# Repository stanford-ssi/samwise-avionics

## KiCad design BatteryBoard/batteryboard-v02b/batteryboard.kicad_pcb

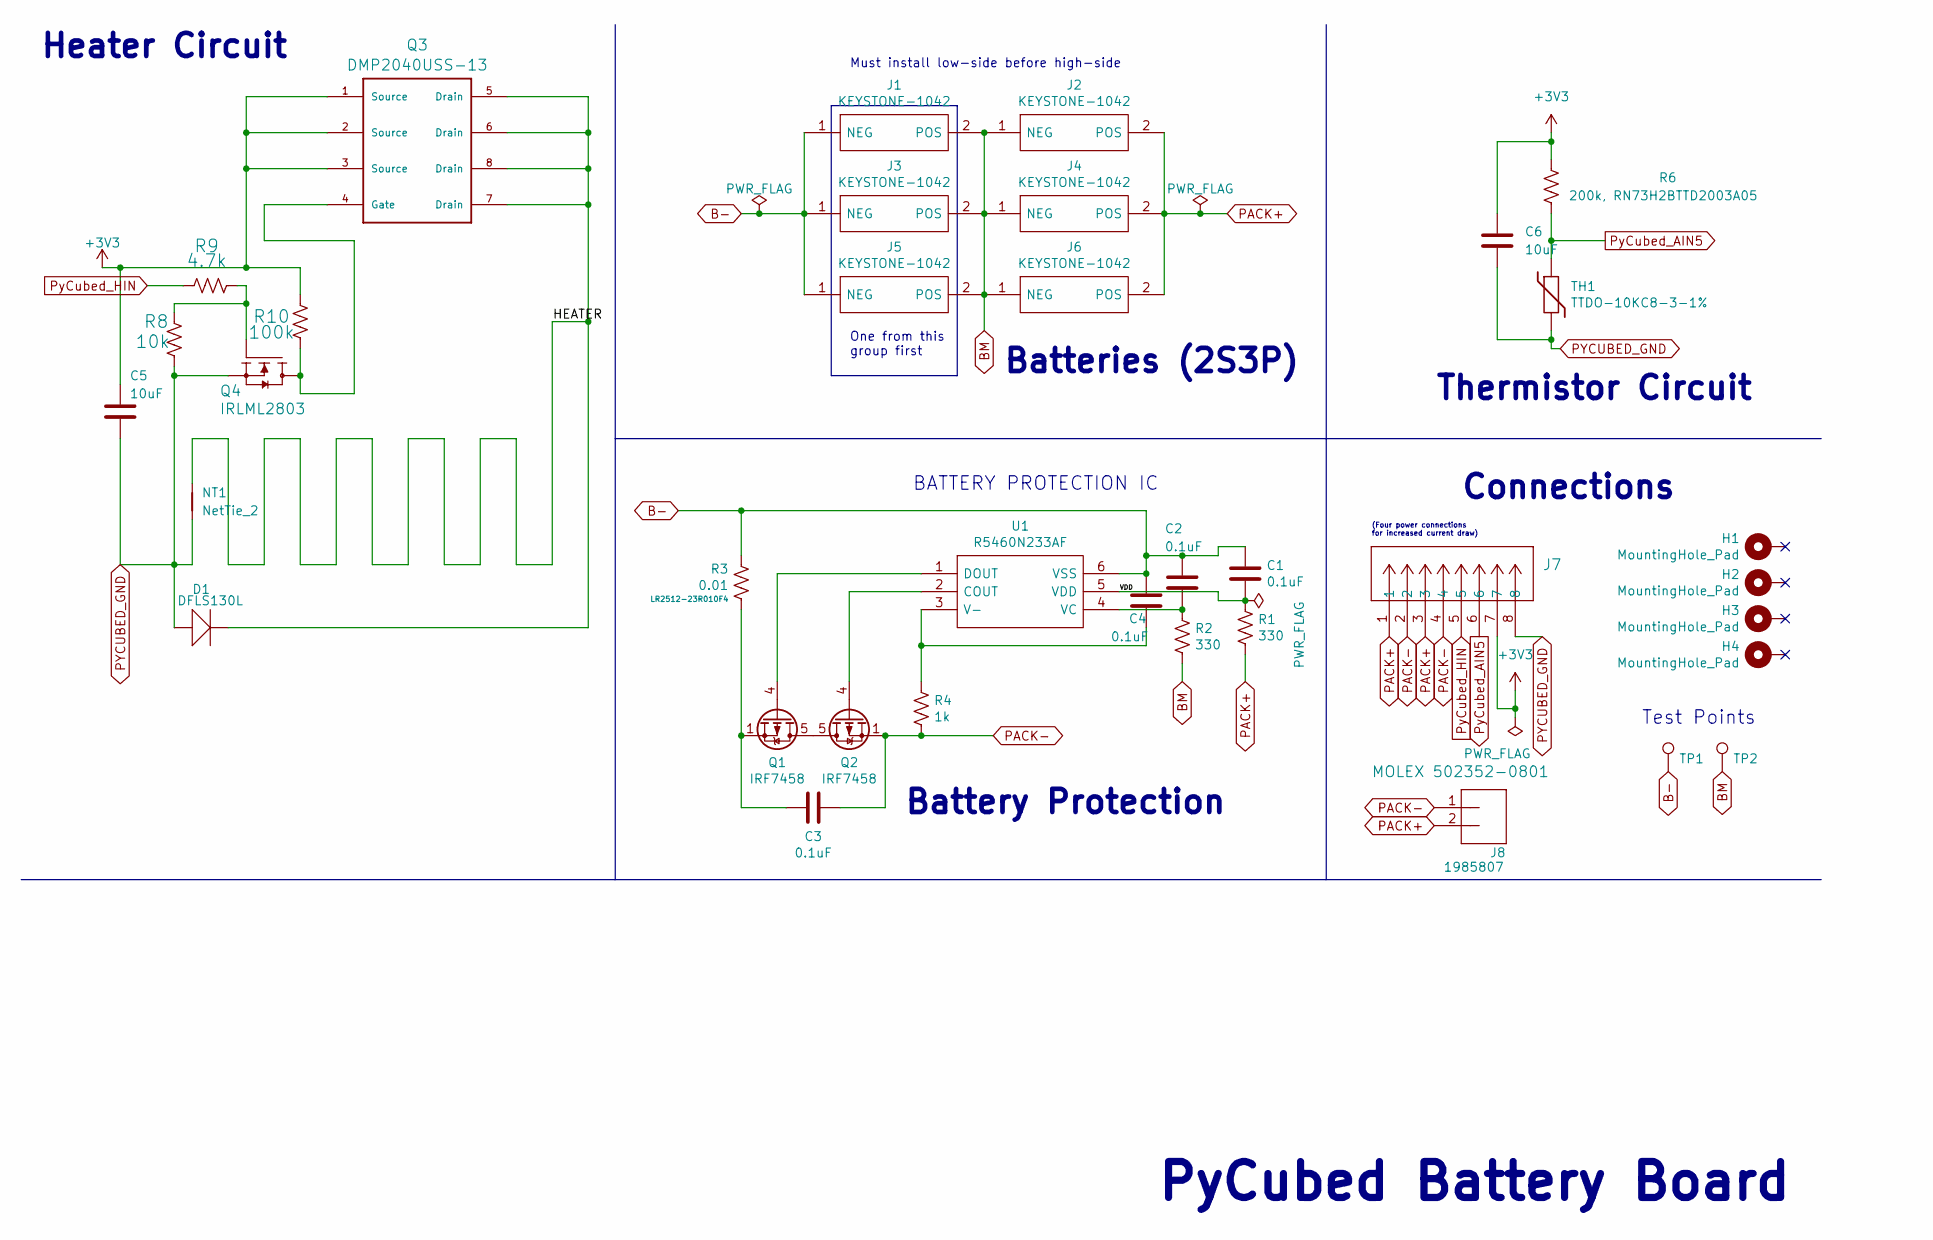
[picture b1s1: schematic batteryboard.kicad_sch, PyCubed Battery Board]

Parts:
C1, C2, C3, C4: 0.1uF; C_0603_1608Metric
C5, C6: 10uF; C_0603_1608Metric
D1: DFLS130L; PWRDI-123
H1, H2, H3, H4: MountingHole_Pad; MountingHole_3.2mm_M3_DIN965_PadMOD
J1, J2, J3, J4, J5, J6: KEYSTONE-1042; Keystone_1042; Manufacturer_Part_Number 1042; Mouser Part Number 534-1042
J7: MOLEX 502352-0801; Molex_502352-0801
J8: 1985807
NT1: NetTie_2; NetTie-2_SMD_Pad0.5mm
Q1, Q2: IRF7458; SOIC-8_3.9x4.9mm_P1.27mm
Q3: DMP2040USS-13
Q4: IRLML2803; SOT-23; Manufacturer_Part_Number MMBT2222AT
R1, R2: 330; R_0603_1608Metric
R3: 0.01; R_2512_6332Metric
R4: 1k; R_0603_1608Metric; Manufacturer_Part_Number LR2512-23R010F4
R6: 200k, RN73H2BTTD2003A05; R_1206_3216Metric
R8: 10k; R_0603_1608Metric
R9: 4.7k; R_0603_1608Metric
R10: 100k; R_0603_1608Metric
TH1: TTDO-10KC8-3-1%; R_Axial_DIN0204_L3.6mm_D1.6mm_P5.08mm_Horizontal
TP1, TP2: TestPoint; TestPoint_Loop_D1.80mm_Drill1.0mm_Beaded
U1: R5460N233AF; SOT-23-6; Manufacturer_Part_Number R5460N233AF-TR-FE; Mouser Part Number 848-R5460N233AFTRFE

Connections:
+3V3: C5.1, C6.1, J7.7, Q3.1 (Source), Q3.2 (Source), Q3.3 (Source), R6.1, R10.2
/HEATER: D1.C, NT1.2, Q3.5 (Drain), Q3.6 (Drain), Q3.7 (Drain), Q3.8 (Drain)
/VDD: C1.2, R1.2, U1.5 (VDD)
B-: C1.1, C2.1, C4.1, J1.1 (NEG), J3.1 (NEG), J5.1 (NEG), R3.1, TP1.1, U1.6 (VSS)
BM: J1.2 (POS), J2.1 (NEG), J3.2 (POS), J4.1 (NEG), J5.2 (POS), J6.1 (NEG), R2.1, TP2.1
unnamed: C3.1, Q1.1 (S), Q1.2 (S), Q1.3 (S), R3.2
unnamed: Q1.5 (D), Q1.6 (D), Q1.7 (D), Q1.8 (D), Q2.5 (D), Q2.6 (D), Q2.7 (D), Q2.8 (D)
unnamed: Q1.4 (G), U1.1 (DOUT)
unnamed: Q2.4 (G), U1.2 (COUT)
unnamed: Q3.4 (Gate), Q4.3 (D), R10.1
unnamed: Q4.1 (G), R8.1, R9.1
unnamed: C4.2, R4.1, U1.3 (V-)
unnamed: C2.2, R2.2, U1.4 (VC)
PACK+: J2.2 (POS), J4.2 (POS), J6.2 (POS), J7.1, J7.3, J8.2, R1.1
PACK-: C3.2, J7.2, J7.4, J8.1, Q2.1 (S), Q2.2 (S), Q2.3 (S), R4.2
PYCUBED_GND: C5.2, C6.2, D1.A, J7.8, NT1.1, Q4.2 (S), R8.2, TH1.2
PyCubed_AIN5: J7.6, R6.2, TH1.1
PyCubed_HIN: J7.5, R9.2

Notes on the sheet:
Connections
(Four power connections for increased current draw)
One from this group first
PyCubed Battery Board
Batteries (2S3P)
Heater Circuit
Test Points
Battery Protection
Must install low-side before high-side
Thermistor Circuit
BATTERY PROTECTION IC

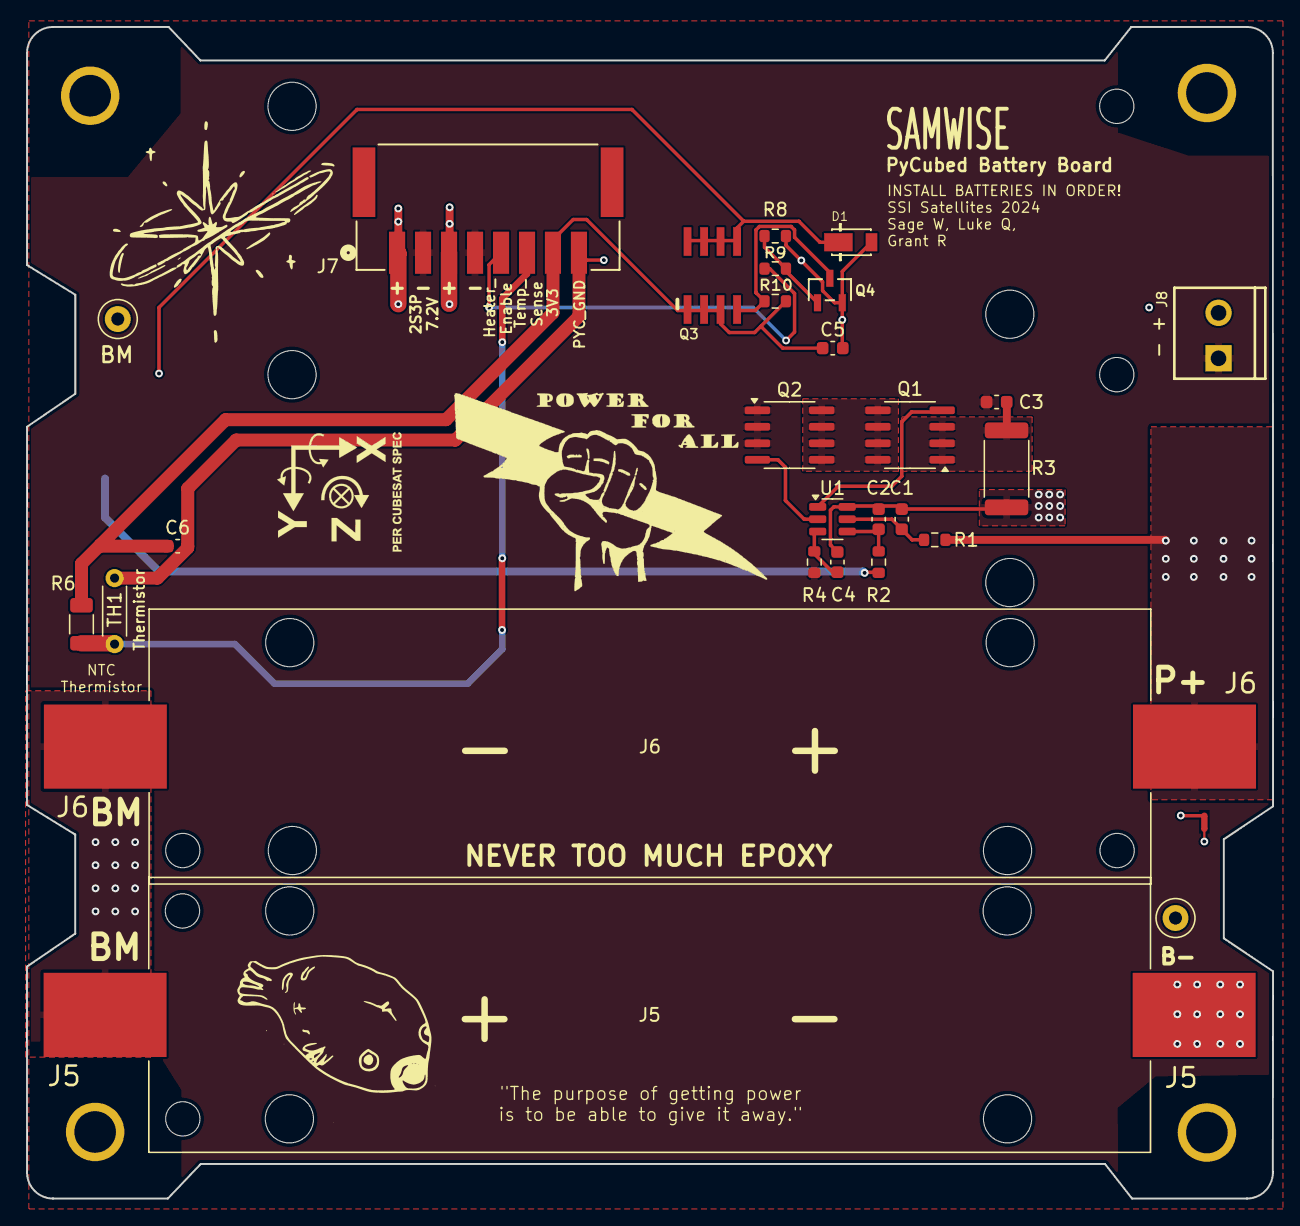
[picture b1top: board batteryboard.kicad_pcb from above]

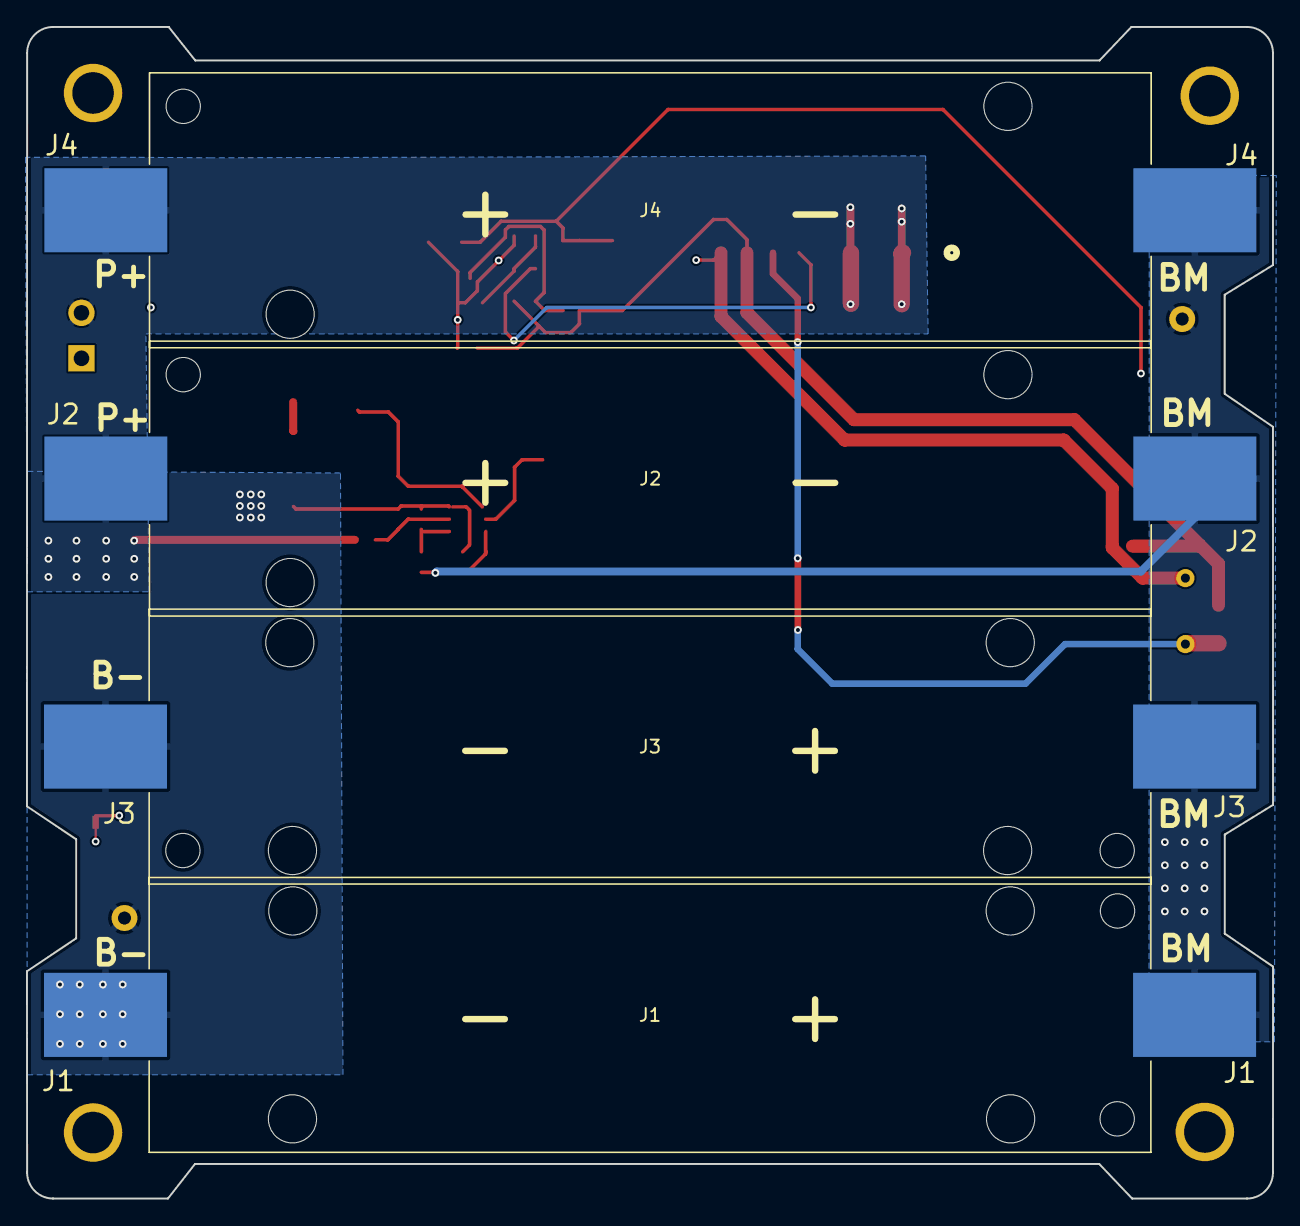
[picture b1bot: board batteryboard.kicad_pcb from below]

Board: 4 copper layers, 95.9 x 90.2 mm, 38 parts (5 on the bottom side), 18 nets.

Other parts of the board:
Ref**: Val**; PowerLogo
Ref**#2: Val**; XYZ_cubesat-bot

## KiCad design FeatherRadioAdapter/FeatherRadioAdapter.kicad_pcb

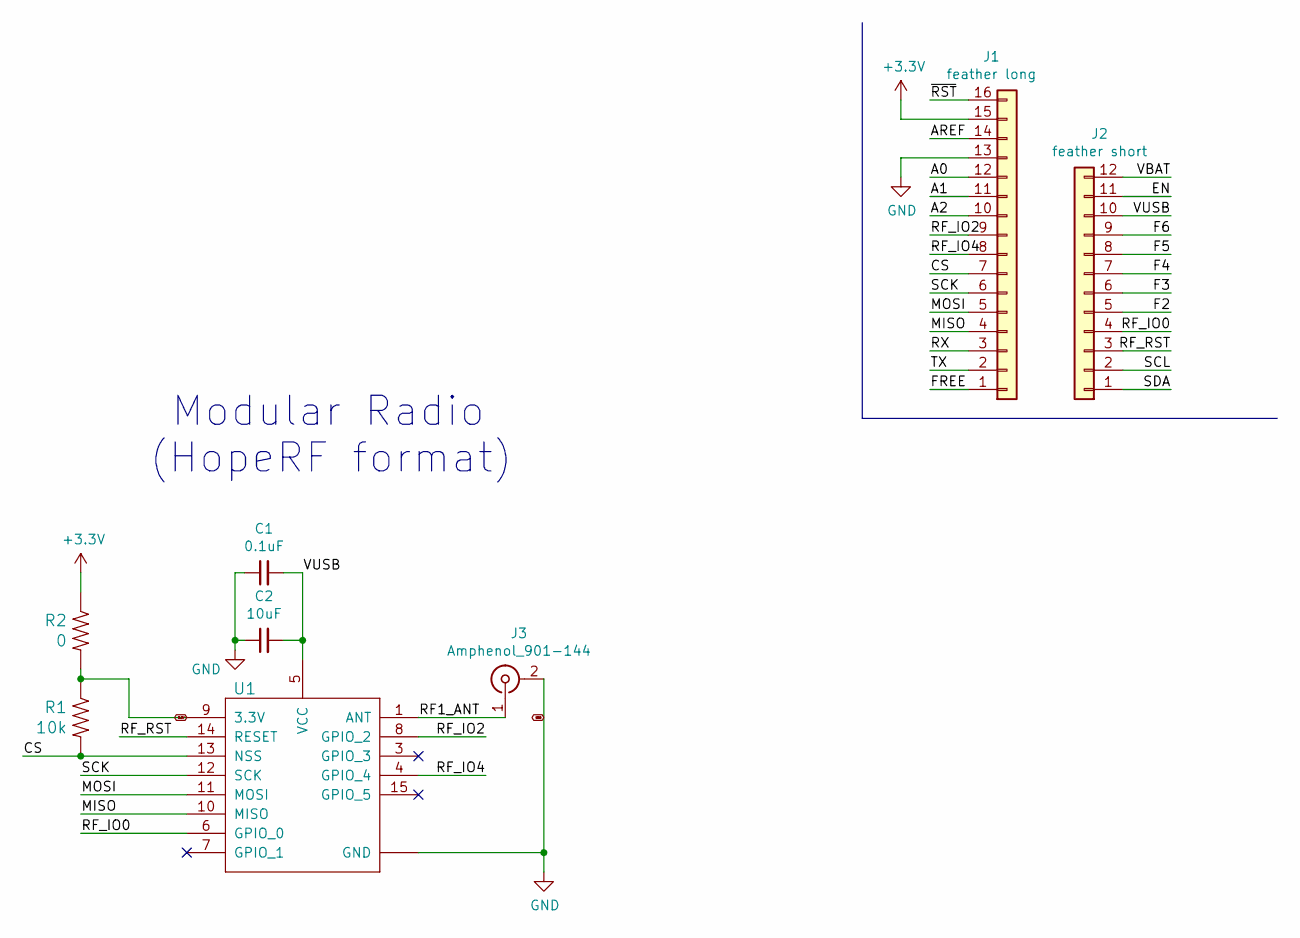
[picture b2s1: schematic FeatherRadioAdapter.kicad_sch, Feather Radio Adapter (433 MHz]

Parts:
C1: 0.1uF; C_0603_1608Metric
C2: 10uF; C_0603_1608Metric
J1: feather long; PinHeader_1x16_P2.54mm_Vertical
J2: feather short; PinHeader_1x12_P2.54mm_Vertical
J3: Amphenol_901-144; SMA_901-144-horizontal; Manufacturer_Part_Number 901-144
R1: 10k; R_0603_1608Metric
R2: 0; R_0603_1608Metric
U1: RFM98PW; RFM95PW; Manufacturer_Part_Number RFM98PW

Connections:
3.3V: R1.1, R2.2, U1.9 (3.3V)
+3V3: J1.15, R2.1
/A0: J1.12
/A1: J1.11
/A2: J1.10
/AREF: J1.14
/CS: J1.7, R1.2, U1.13 (NSS)
/EN: J2.11
/F2: J2.5
/F3: J2.6
/F4: J2.7
/F5: J2.8
/F6: J2.9
/FREE: J1.1
/MISO: J1.4, U1.10 (MISO)
/MOSI: J1.5, U1.11 (MOSI)
/RF1_ANT: J3.1 (In), U1.1 (ANT)
/RF_IO0: J2.4, U1.6 (GPIO_0)
/RF_IO2: J1.9, U1.8 (GPIO_2)
/RF_IO4: J1.8, U1.4 (GPIO_4)
/RF_RST: J2.3, U1.14 (RESET)
/RX: J1.3
/SCK: J1.6, U1.12 (SCK)
/SCL: J2.2
/SDA: J2.1
/TX: J1.2
/VBAT: J2.12
/VUSB: C1.2, C2.2, J2.10, U1.5 (VCC)
/~RST: J1.16
GND: C1.1, C2.1, J1.13, J3.2 (Ext), U1.2 (GND), U1.16 (GND), U1.17 (GND)

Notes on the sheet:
Modular Radio (HopeRF format)

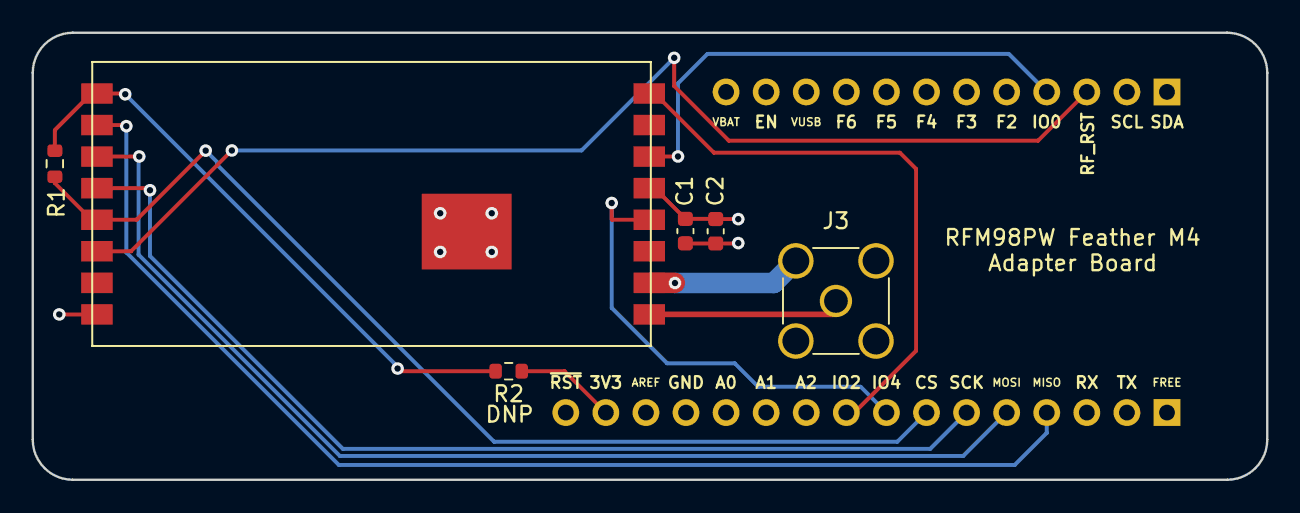
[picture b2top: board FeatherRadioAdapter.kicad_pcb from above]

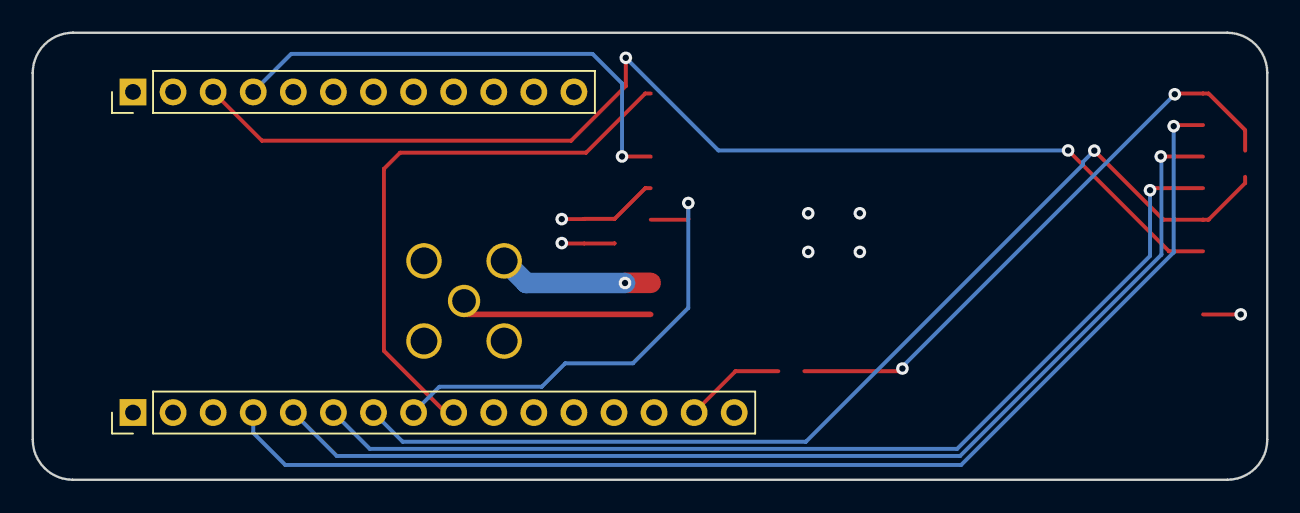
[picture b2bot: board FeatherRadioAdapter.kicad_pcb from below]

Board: 4 copper layers, 78.2 x 28.3 mm, 8 parts (2 on the bottom side), 13 nets.

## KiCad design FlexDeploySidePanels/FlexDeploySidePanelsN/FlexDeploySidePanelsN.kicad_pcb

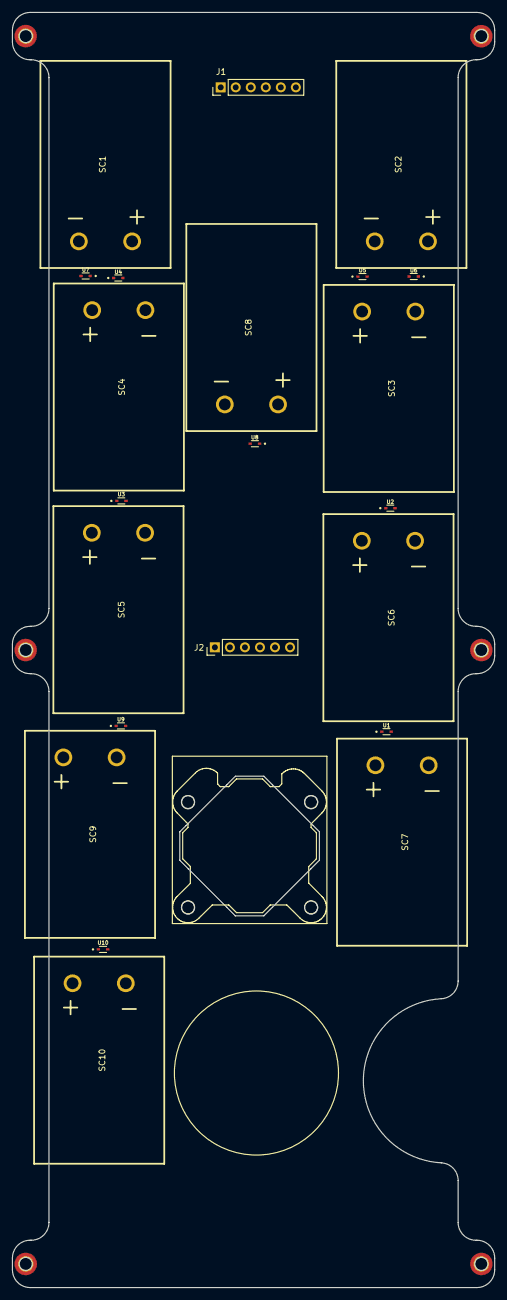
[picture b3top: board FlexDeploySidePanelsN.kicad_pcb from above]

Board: 4 copper layers, 81.5 x 215.5 mm, 29 parts (1 on the bottom side), 17 nets, no tracks yet.

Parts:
H1, H2, H5, H9, H13, H17: MountingHole_Pad; MountingHole_2.2mm_M2_DIN965_Pad_TopBottom
J1, J2: Through_Hole_1; PinHeader_1x06_P2.54mm_Vertical
J3: MOLEX_2053380006
SC1, SC2, SC3, SC4, SC5, SC6, SC7, SC8, SC9, SC10: SM101K07TF
U1, U2, U3, U4, U5, U6, U7, U8, U9, U10: BAS70-02V-G3-08

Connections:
GND: H1.1, H2.1, H5.1, H9.1, H13.1, H17.1, J1.1, J1.2, J1.3, SC8.2 (-), U8.0 (A)
unnamed: J2.1, J3.1
unnamed: J2.2, J3.2
unnamed: J2.3, J3.3
unnamed: J2.4, J3.4
unnamed: J2.5, J3.5
unnamed: J2.6, J3.6
unnamed: SC1.1 (+), SC2.2 (-), U6.0 (A), U7.1 (C)
unnamed: SC1.2 (-), SC8.1 (+), U7.0 (A), U8.1 (C)
unnamed: SC2.1 (+), SC3.2 (-), U5.0 (A), U6.1 (C)
unnamed: SC3.1 (+), SC4.2 (-), U4.0 (A), U5.1 (C)
unnamed: SC4.1 (+), SC5.2 (-), U3.0 (A), U4.1 (C)
unnamed: SC5.1 (+), SC6.2 (-), U2.0 (A), U3.1 (C)
unnamed: SC6.1 (+), SC7.2 (-), U1.0 (A), U2.1 (C)
unnamed: SC9.2 (-), SC10.1 (+), U9.0 (A), U10.1 (C)
unnamed: SC7.1 (+), SC10.2 (-), U1.1 (C), U10.0 (A)
VSOLAR: J1.4, J1.5, J1.6, SC9.1 (+), U9.1 (C)

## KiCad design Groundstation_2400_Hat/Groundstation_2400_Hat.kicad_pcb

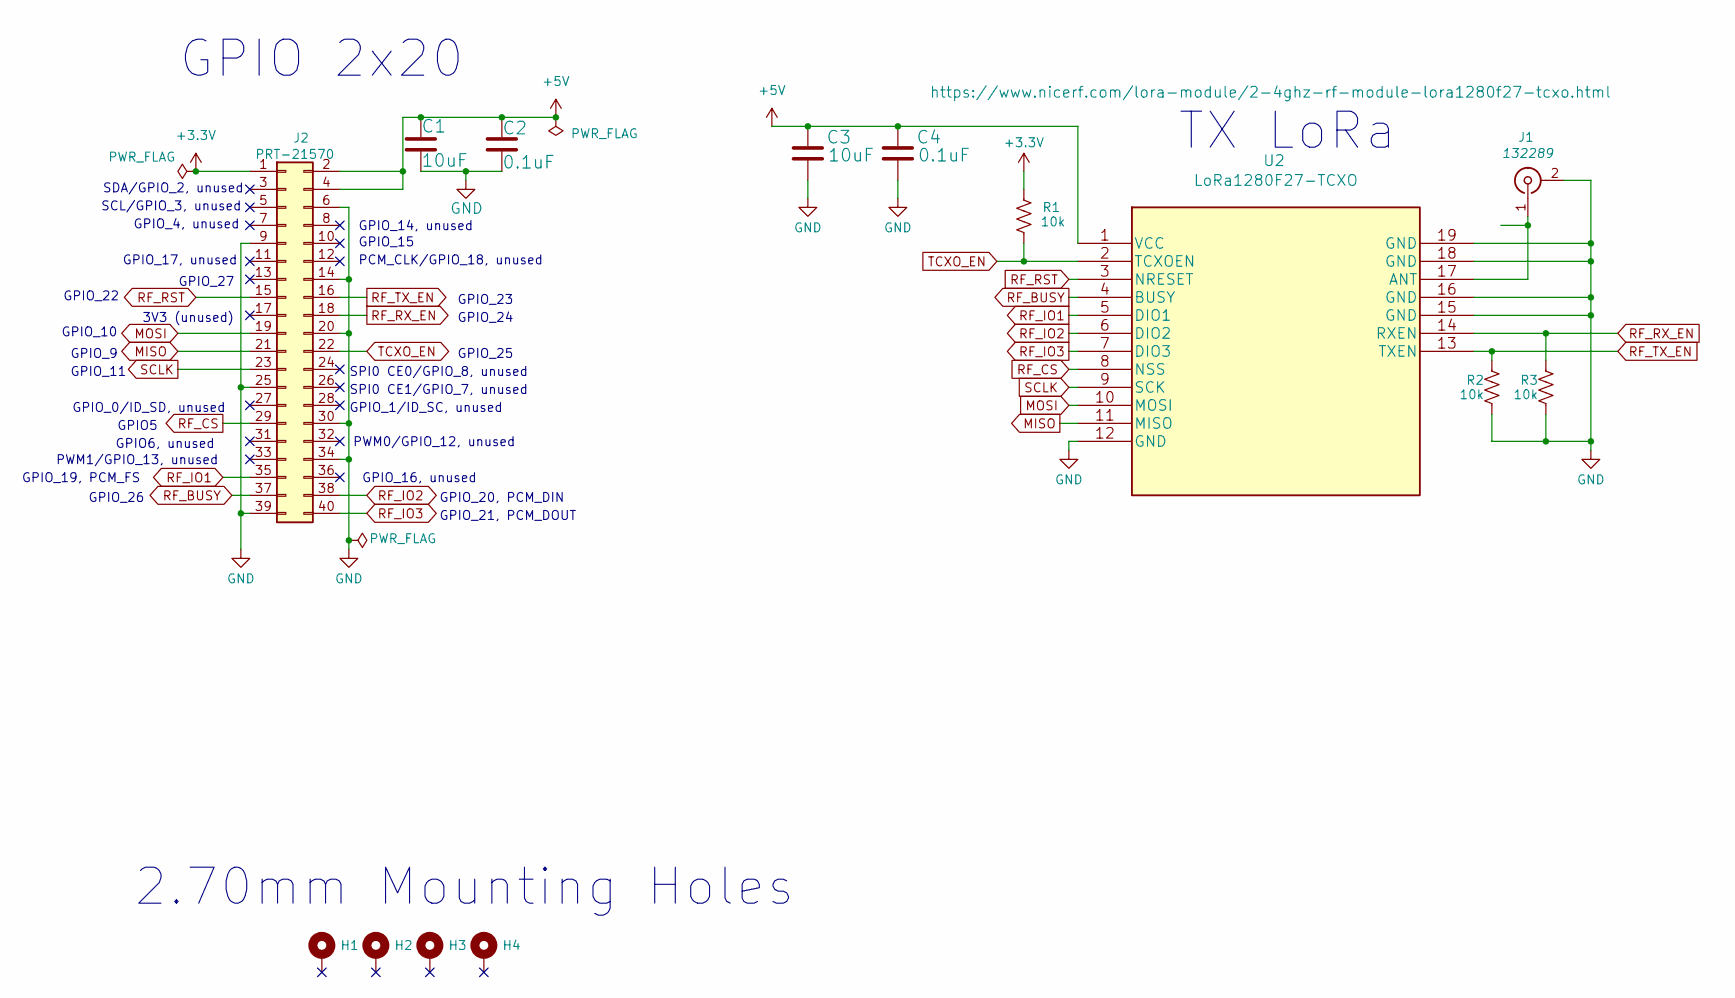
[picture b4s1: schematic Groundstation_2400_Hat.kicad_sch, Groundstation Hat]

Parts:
C1, C3: 10uF; C_0603_1608Metric
C2, C4: 0.1uF; C_0603_1608Metric
H1, H2, H3, H4: MountingHole; MountingHole_2.7mm_M2.5_DIN965_Pad
J1: 132289; SMA_Amphenol_132289_EdgeMount_groundstation; Manufacturer_Part_Number 132289
J2: PRT-21570
R1, R2, R3: 10k; R_0603_1608Metric
U2: LoRa1280F27-TCXO; LORA128XF27

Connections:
+3.3V: J2.1, R1.1
+5V: C1.1, C2.1, C3.1, C4.1, J2.2, J2.4, U2.1 (VCC)
GND: C1.2, C2.2, C3.2, C4.2, J1.2 (Ext), J2.6, J2.9, J2.14, J2.20, J2.25, J2.30, J2.34, J2.39, R2.1, R3.1, U2.12 (GND), U2.15 (GND), U2.16 (GND), U2.18 (GND), U2.19 (GND)
MISO: J2.21, U2.11 (MISO)
MOSI: J2.19, U2.10 (MOSI)
unnamed: J1.1 (In), U2.17 (ANT)
RF_BUSY: J2.37, U2.4 (BUSY)
RF_CS: J2.29, U2.8 (NSS)
RF_IO1: J2.35, U2.5 (DIO1)
RF_IO2: J2.38, U2.6 (DIO2)
RF_IO3: J2.40, U2.7 (DIO3)
RF_RST: J2.15, U2.3 (NRESET)
RF_RX_EN: J2.18, R3.2, U2.14 (RXEN)
RF_TX_EN: J2.16, R2.2, U2.13 (TXEN)
SCLK: J2.23, U2.9 (SCK)
TCXO_EN: J2.22, R1.2, U2.2 (TCXOEN)

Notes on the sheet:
GPIO_21, PCM_DOUT
PCM_CLK/GPIO_18, unused
SCL/GPIO_3, unused
GPIO_14, unused
GPIO_24
PWM1/GPIO_13, unused
PWM0/GPIO_12, unused
GPIO_20, PCM_DIN
GPIO_17, unused
SDA/GPIO_2, unused
GPIO_9
GPIO5
GPIO_23
GPIO_19, PCM_FS
GPIO_4, unused
GPIO_11
GPIO_22
GPIO_25
SPI0 CE1/GPIO_7, unused
SPI0 CE0/GPIO_8, unused
GPIO_27
GPIO_15
2.70mm Mounting Holes
3V3 (unused)
TX LoRa
GPIO_16, unused
GPIO_0/ID_SD, unused
GPIO_26
GPIO_10
GPIO6, unused
GPIO 2x20
GPIO_1/ID_SC, unused

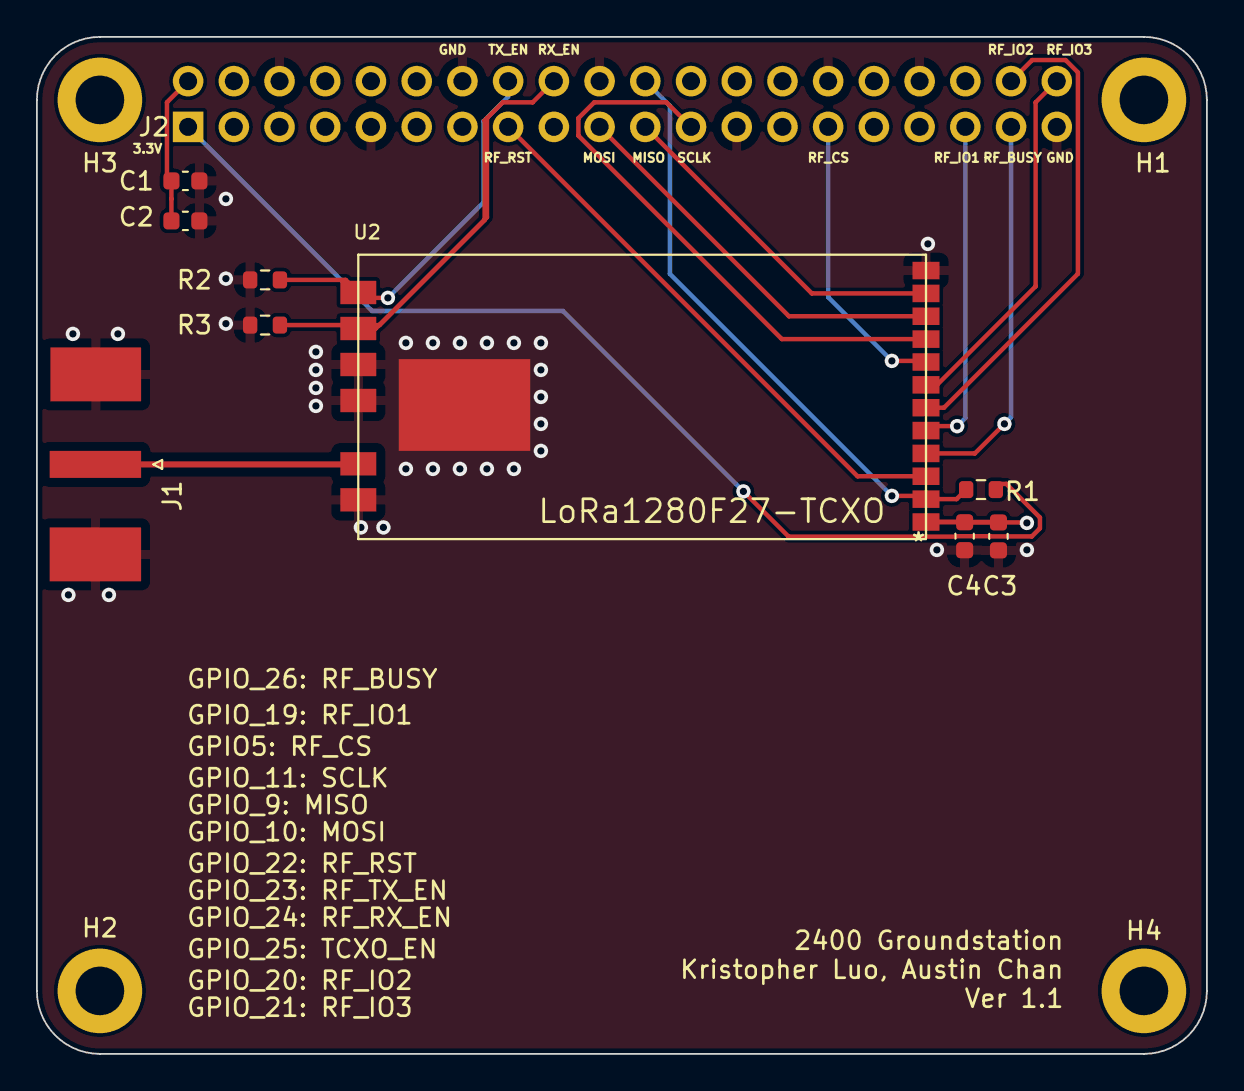
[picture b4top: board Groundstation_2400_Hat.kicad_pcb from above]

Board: 4 copper layers, 65.0 x 56.5 mm, 14 parts (1 on the bottom side), 16 nets.

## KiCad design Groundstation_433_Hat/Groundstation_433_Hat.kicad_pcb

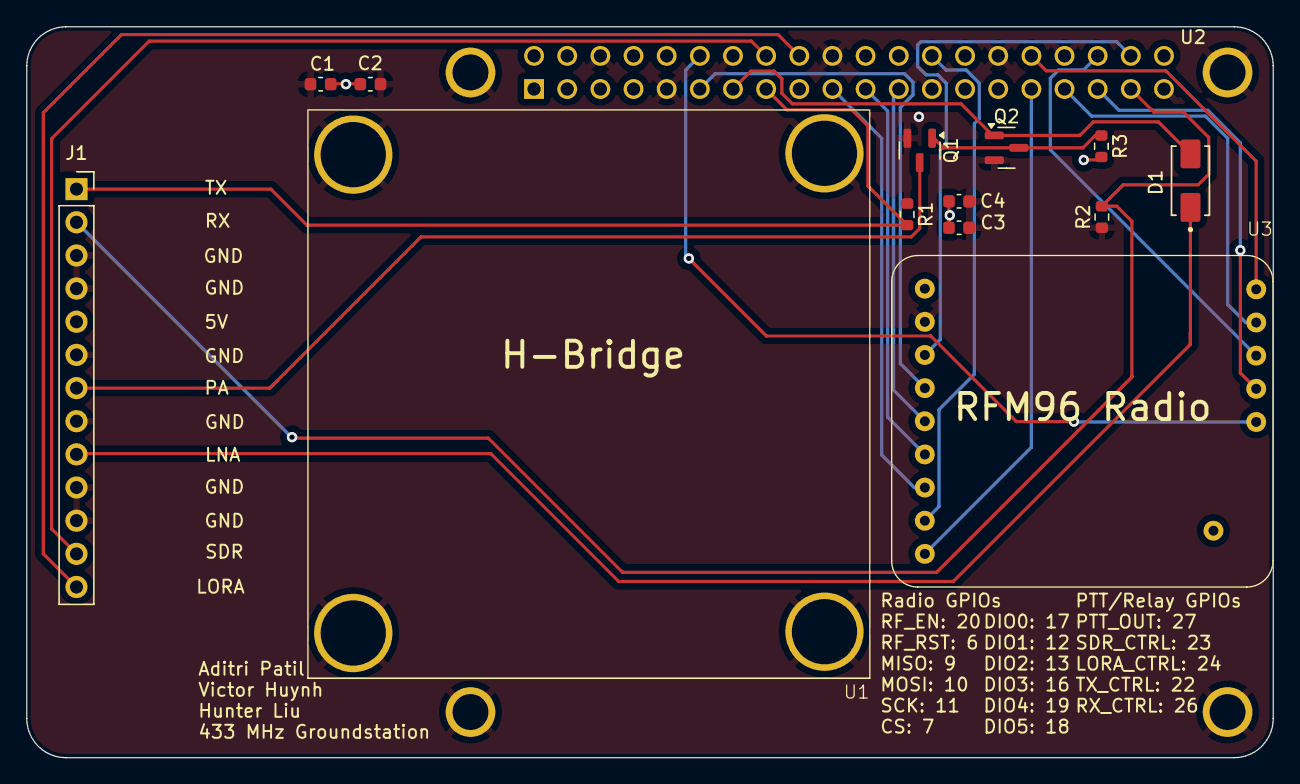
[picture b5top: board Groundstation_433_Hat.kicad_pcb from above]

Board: 4 copper layers, 95.5 x 56.0 mm, 14 parts (0 on the bottom side), 22 nets.

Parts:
C1, C3: 10uF; C_0603_1608Metric
C2, C4: 0.1uF; C_0603_1608Metric
D1: M7
J1: Conn_01x13_Pin; PinSocket_1x13_P2.54mm_Vertical
Q1, Q2: 2N7002; SOT-23
R1, R2: 10k; R_0603_1608Metric
R3: 100k; R_0603_1608Metric
U1: L298N_Module; H-bridge module
U2: Raspberry_Pi_4B
U3: RFM96W

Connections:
+5V: C1.1, C2.1, C3.1, C4.1, J1.5, R3.2, U2.2 (5V), U2.4 (5V), U3.1 (Vin)
/433_hat_board/CS: U2.26 (GPIO7/~SPI_CE1), U3.8 (CS)
/433_hat_board/DIO0: U2.11 (GPIO17/GPIO_GEN0), U3.4 (DIO0)
/433_hat_board/DIO1: U2.32 (GPIO12), U3.10 (DIO1)
/433_hat_board/DIO2: U2.33 (GPIO13), U3.11 (DIO2)
/433_hat_board/DIO3: U2.36 (GPIO16), U3.12 (DIO3)
/433_hat_board/DIO4: U2.35 (GPIO19), U3.13 (DIO4)
/433_hat_board/DIO5: U2.12 (GPIO18/GPIO_GEN1), U3.14 (DIO5)
/433_hat_board/MISO: U2.21 (GPIO9/SPI_MISO), U3.6 (MISO)
/433_hat_board/MOSI: U2.19 (GPIO10/SPI_MOSI), U3.7 (MOSI)
/433_hat_board/PTT_OUT: D1.A, Q2.1 (G), U2.13 (GPIO27/GPIO_GEN2)
/433_hat_board/RST: U2.31 (GPIO6), U3.9 (RST)
/433_hat_board/SCK: U2.23 (GPIO11/SPI_SCLK), U3.5 (SCK)
/433_hat_board/enable: U2.38 (GPIO20), U3.3 (EN)
/LORA_CTRL: J1.13, U2.18 (GPIO24/GPIO_GEN5)
/RX_CTRL: J1.2, R2.2, U2.37 (GPIO26)
/SDR_CTRL: J1.12, U2.16 (GPIO23/GPIO_GEN4)
/TX_CTRL: J1.1, R1.2, U2.15 (GPIO22/GPIO_GEN3)
GND: C1.2, C2.2, C3.2, C4.2, J1.3, J1.4, J1.6, J1.8, J1.10, J1.11, Q1.2 (S), Q2.2 (S), R1.1, R2.1, U1.4 (GND), U2.6 (GND), U2.9 (GND), U2.14 (GND), U2.20 (GND), U2.25 (GND), U2.30 (GND), U2.34 (GND), U2.39 (GND), U2.S1 (SHIELD), U2.S2 (SHIELD), U2.S3 (SHIELD), U2.S4 (SHIELD), U3.2 (GND)
LNA_PTT: D1.C, J1.9
unnamed: Q1.1 (G), Q2.3 (D), R3.1
PA_PTT: J1.7, Q1.3 (D)

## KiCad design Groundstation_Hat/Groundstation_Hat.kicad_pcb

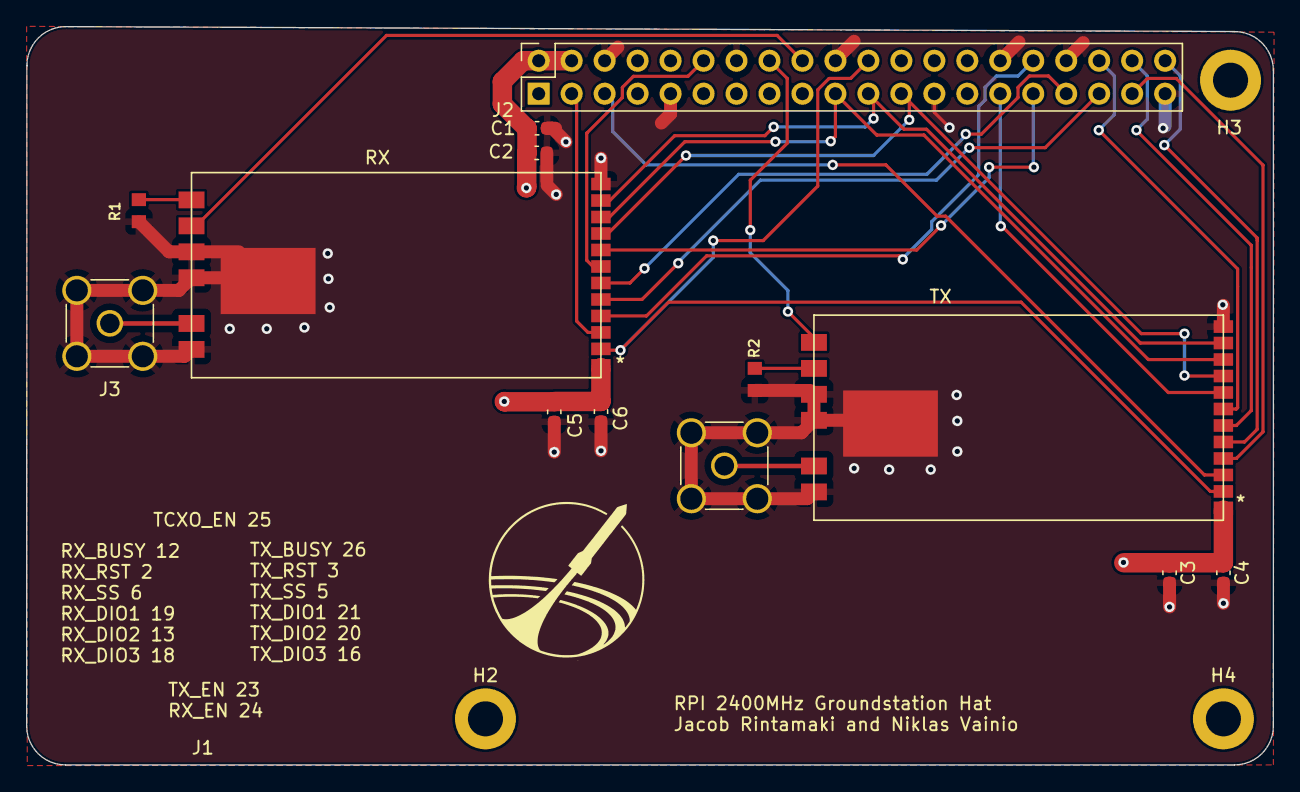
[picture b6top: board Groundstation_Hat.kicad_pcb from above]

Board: 4 copper layers, 96.1 x 56.9 mm, 16 parts (0 on the bottom side), 24 nets.

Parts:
C1, C3, C5: 10uF; C_0603_1608Metric
C2, C4, C6: 0.1uF; C_0603_1608Metric
H2, H3, H4: MountingHole; MountingHole_2.7mm_M2.5_DIN965_Pad
J1, J3: Amphenol_901-144; SMA_901-144
J2: PRT-21570
R1, R2: 10KOHM-1_10W-1%(0603)0603; R0603
U1, U2: LoRa1280F27-TCXO; LORA128XF27

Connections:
+5V: C1.1, C2.1, C3.1, C4.1, C5.1, C6.1, J2.2, J2.4, U1.1 (VCC), U2.1 (VCC)
GND: C1.2, C2.2, C3.2, C4.2, C5.2, C6.2, J1.2 (Ext), J2.6, J2.9, J2.14, J2.20, J2.25, J2.30, J2.34, J2.39, J3.2 (Ext), R1.1, R2.1, U1.12 (GND), U1.15 (GND), U1.16 (GND), U1.18 (GND), U1.19 (GND), U2.12 (GND), U2.15 (GND), U2.16 (GND), U2.18 (GND), U2.19 (GND)
MISO: J2.21, U1.11 (MISO), U2.11 (MISO)
MOSI: J2.19, U1.10 (MOSI), U2.10 (MOSI)
unnamed: J1.1 (In), U2.17 (ANT)
unnamed: J3.1 (In), U1.17 (ANT)
unnamed: R1.2, U1.13 (TXEN)
unnamed: R2.2, U2.14 (RXEN)
RF_IO1: J2.40, U2.5 (DIO1)
RF_IO2: J2.38, U2.6 (DIO2)
RF_IO3: J2.36, U2.7 (DIO3)
RF_IO4: J2.35, U1.5 (DIO1)
RF_IO5: J2.33, U1.6 (DIO2)
RF_IO6: J2.12, U1.7 (DIO3)
RF_RX_EN: J2.18, U1.14 (RXEN)
RF_TX_EN: J2.16, U2.13 (TXEN)
RX_BUSY: J2.32, U1.4 (BUSY)
RX_CS: J2.31, U1.8 (NSS)
RX_RST: J2.3, U1.3 (NRESET)
SCLK: J2.23, U1.9 (SCK), U2.9 (SCK)
TCXO_EN: J2.22, U1.2 (TCXOEN), U2.2 (TCXOEN)
TX_BUSY: J2.37, U2.4 (BUSY)
TX_CS: J2.29, U2.8 (NSS)
TX_RST: J2.5, U2.3 (NRESET)

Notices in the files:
parts and their libraries:
Copyright 2021 Accelerated Designs. All rights reserved.
